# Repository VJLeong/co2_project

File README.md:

#  Automated Compensation of Environmental Changes on CO2 Gas Sensor Response
Project Supervisor: Dr. Ajay Achath Mohanan <br>
Project Members: Leong Van Jun, Vincent Law Yun Kae <br>
Project Commence Date: November 2024 - Present <br>
## Project Description <br>
The main objective of the project is to introduce Artificial Intelligence (AI) and/or machine learning (ML) tools to assist in analysing patterns in obtained carbon dioxide sensor readings and filtering of unwanted noises. <br>
This objective is achieved through proper setting up of the hardware setup and environment of the carbon dioxide sensor. Which is achieved by constructing of appropriate PCB and testing through external microcontroller units. <br>
For this project, the microcontroller unit used is the PSoC 5LP module and PCB design software used is Kicad 8.

## Changelog
### 13/5/2025:
  - Redesigned second version of external chamber PCB --  ready for remanufacturing if needed
  - Updated PID controller for heater controls to P controller (Kp = 120.0f)
### 18/4/2025:
  - Added external chamber PCB schematic design into the repo
  - Begin testing with external chamber PCB prototype
### 23/3/2025:
  - Updated capacitance.py to remove KNN cluster and median filtering algorithm to display raw data output in graph
  - Added heater PID bang-bang control and temperature sensor (3/3 tasks)
### 3/3/2025:
  - Written Python script involving KNN machine learning algorithm to help effeciently filter outlier values in read capacitance values
### 22/2/2025:
  - Re-updated read_capacitance function
  - Included improved analogue circuitry to measure capacitance, now using an
    NE556N timer module instead of simple RC circuit (LTSpice file included!)
### 13/2/2025:
  - Completed two tasks of three: Measure capacitance via PSoC
  - Currently debugging capacitance value, current capacitance value too small!
### 12/2/2025: 
  - Uploaded PSoC Creator and Kicad project files into Github repo for the first time.
  - Completed one task of three: Interface SCD30 on PCB with PSoC 5LP to obtain CO2 concentration, temperature, and relative humidity levels (rh%)

## Reference Materials
SCD30 item website: https://sensirion.com/products/catalog/SCD30 <br>
SCD30 Datasheet: https://sensirion.com/media/documents/4EAF6AF8/61652C3C/Sensirion_CO2_Sensors_SCD30_Datasheet.pdf <br>
SCD30 Interface Description: https://sensirion.com/media/documents/D7CEEF4A/6165372F/Sensirion_CO2_Sensors_SCD30_Interface_Description.pdf <br>
SCD30 Example Code: https://github.com/Sensirion/embedded-scd/releases/tag/2.1.1 <br>

## Acknowledgement
Thank you to Dr. Ajay for his supervision and guidance for the project members throughout the project duration.

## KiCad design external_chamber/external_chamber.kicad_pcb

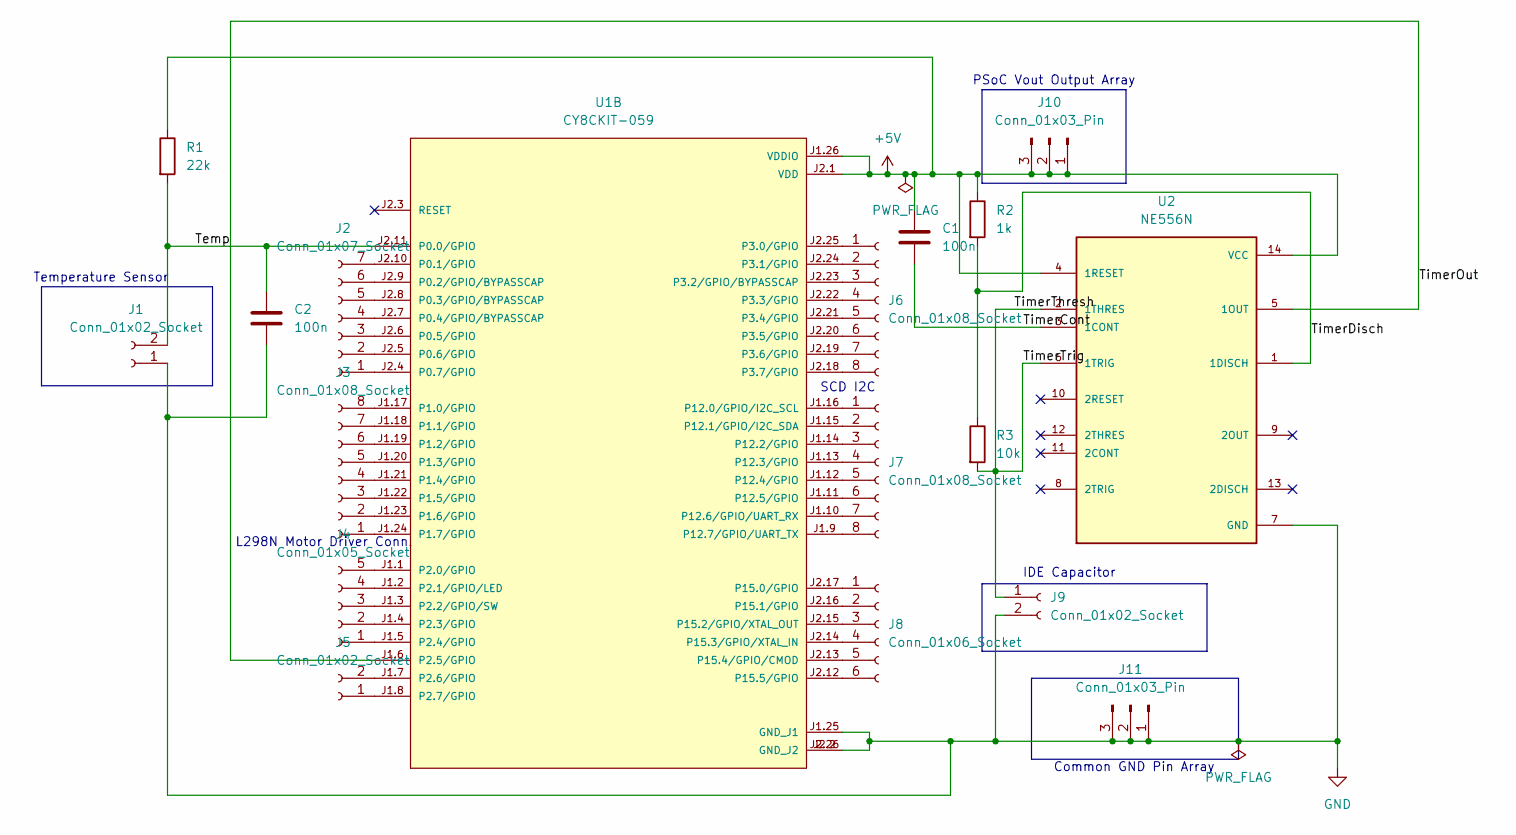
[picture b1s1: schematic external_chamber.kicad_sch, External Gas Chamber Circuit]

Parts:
C1, C2: 100n; C_Disc_D5.0mm_W2.5mm_P5.00mm
J1: Conn_01x02_Socket; PinHeader_1x02_P2.54mm_Vertical
J2: Conn_01x07_Socket; PinSocket_1x07_P2.54mm_Vertical
J3, J6: Conn_01x08_Socket; PinSocket_1x08_P2.54mm_Vertical
J4: Conn_01x05_Socket; PinSocket_1x05_P2.54mm_Vertical
J5, J9: Conn_01x02_Socket; PinSocket_1x02_P2.54mm_Vertical
J7: Conn_01x08_Socket; PinHeader_1x08_P2.54mm_Vertical
J8: Conn_01x06_Socket; PinSocket_1x06_P2.54mm_Vertical
J10, J11: Conn_01x03_Pin; PinSocket_1x03_P2.54mm_Vertical
R1: 22k; R_Axial_DIN0207_L6.3mm_D2.5mm_P7.62mm_Horizontal
R2: 1k; R_Axial_DIN0207_L6.3mm_D2.5mm_P7.62mm_Horizontal
R3: 10k; R_Axial_DIN0207_L6.3mm_D2.5mm_P7.62mm_Horizontal
U1: CY8CKIT-059; MODULE_CY8CKIT-059; PARTREV G
U2: NE556N; DIP794W45P254L1930H508Q14; PARTREV JUNE 2006; DigiKey_Part_Number 296-6504-5-ND

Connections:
+5V: C1.1, J10.1, J10.2, J10.3, R1.1, R2.1, U1.J1.26 (VDDIO), U1.J2.1 (VDD), U2.4 (1RESET), U2.14 (VCC)
/Temp: C2.1, J1.2, R1.2, U1.J2.11 (P0.0/GPIO)
/TimerCont: C1.2, U2.3 (1CONT)
/TimerDisch: R2.2, R3.1, U2.1 (1DISCH)
/TimerOut: U1.J1.6 (P2.5/GPIO), U2.5 (1OUT)
/TimerThresh: J9.1, R3.2, U2.2 (1THRES), U2.6 (1TRIG)
GND: C2.2, J1.1, J9.2, J11.1, J11.2, J11.3, U1.J1.25 (GND_J1), U1.J2.2 (GND_J2), U1.J2.26 (GND_J2), U2.7 (GND)
unnamed: J2.1, U1.J2.4 (P0.7/GPIO)
unnamed: J2.2, U1.J2.5 (P0.6/GPIO)
unnamed: J2.3, U1.J2.6 (P0.5/GPIO)
unnamed: J2.4, U1.J2.7 (P0.4/GPIO/BYPASSCAP)
unnamed: J2.5, U1.J2.8 (P0.3/GPIO/BYPASSCAP)
unnamed: J2.6, U1.J2.9 (P0.2/GPIO/BYPASSCAP)
unnamed: J2.7, U1.J2.10 (P0.1/GPIO)
unnamed: J3.1, U1.J1.24 (P1.7/GPIO)
unnamed: J3.2, U1.J1.23 (P1.6/GPIO)
unnamed: J3.3, U1.J1.22 (P1.5/GPIO)
unnamed: J3.4, U1.J1.21 (P1.4/GPIO)
unnamed: J3.5, U1.J1.20 (P1.3/GPIO)
unnamed: J3.6, U1.J1.19 (P1.2/GPIO)
unnamed: J3.7, U1.J1.18 (P1.1/GPIO)
unnamed: J3.8, U1.J1.17 (P1.0/GPIO)
unnamed: J4.1, U1.J1.5 (P2.4/GPIO)
unnamed: J4.2, U1.J1.4 (P2.3/GPIO)
unnamed: J4.3, U1.J1.3 (P2.2/GPIO/SW)
unnamed: J4.4, U1.J1.2 (P2.1/GPIO/LED)
unnamed: J4.5, U1.J1.1 (P2.0/GPIO)
unnamed: J5.1, U1.J1.8 (P2.7/GPIO)
unnamed: J5.2, U1.J1.7 (P2.6/GPIO)
unnamed: J6.1, U1.J2.25 (P3.0/GPIO)
unnamed: J6.2, U1.J2.24 (P3.1/GPIO)
unnamed: J6.3, U1.J2.23 (P3.2/GPIO/BYPASSCAP)
unnamed: J6.4, U1.J2.22 (P3.3/GPIO)
unnamed: J6.5, U1.J2.21 (P3.4/GPIO)
unnamed: J6.6, U1.J2.20 (P3.5/GPIO)
unnamed: J6.7, U1.J2.19 (P3.6/GPIO)
unnamed: J6.8, U1.J2.18 (P3.7/GPIO)
unnamed: J7.1, U1.J1.16 (P12.0/GPIO/I2C_SCL)
unnamed: J7.2, U1.J1.15 (P12.1/GPIO/I2C_SDA)
unnamed: J7.3, U1.J1.14 (P12.2/GPIO)
unnamed: J7.4, U1.J1.13 (P12.3/GPIO)
unnamed: J7.5, U1.J1.12 (P12.4/GPIO)
unnamed: J7.6, U1.J1.11 (P12.5/GPIO)
unnamed: J7.7, U1.J1.10 (P12.6/GPIO/UART_RX)
unnamed: J7.8, U1.J1.9 (P12.7/GPIO/UART_TX)
unnamed: J8.1, U1.J2.17 (P15.0/GPIO)
unnamed: J8.2, U1.J2.16 (P15.1/GPIO)
unnamed: J8.3, U1.J2.15 (P15.2/GPIO/XTAL_OUT)
unnamed: J8.4, U1.J2.14 (P15.3/GPIO/XTAL_IN)
unnamed: J8.5, U1.J2.13 (P15.4/GPIO/CMOD)
unnamed: J8.6, U1.J2.12 (P15.5/GPIO)

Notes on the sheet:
SCD I2C
IDE Capacitor
PSoC Vout Output Array
Common GND Pin Array
Temperature Sensor
L298N Motor Driver Conn.

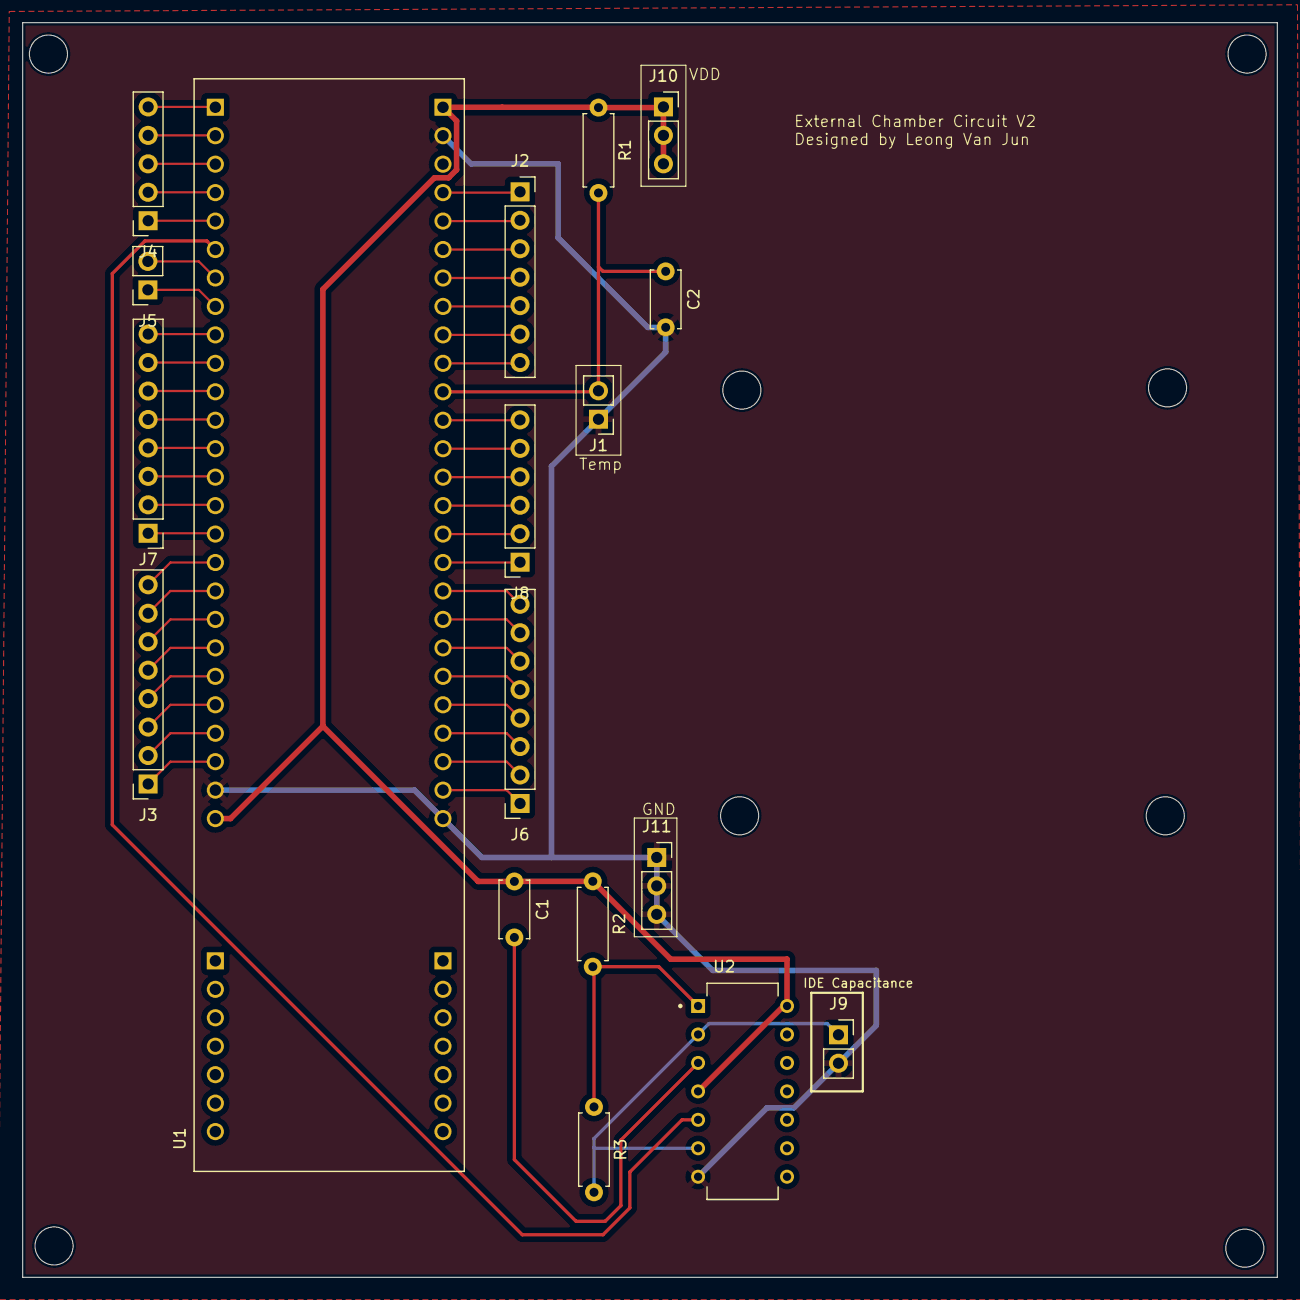
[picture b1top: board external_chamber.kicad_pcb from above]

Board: 2 copper layers, 112.0 x 112.0 mm, 18 parts (0 on the bottom side), 51 nets.

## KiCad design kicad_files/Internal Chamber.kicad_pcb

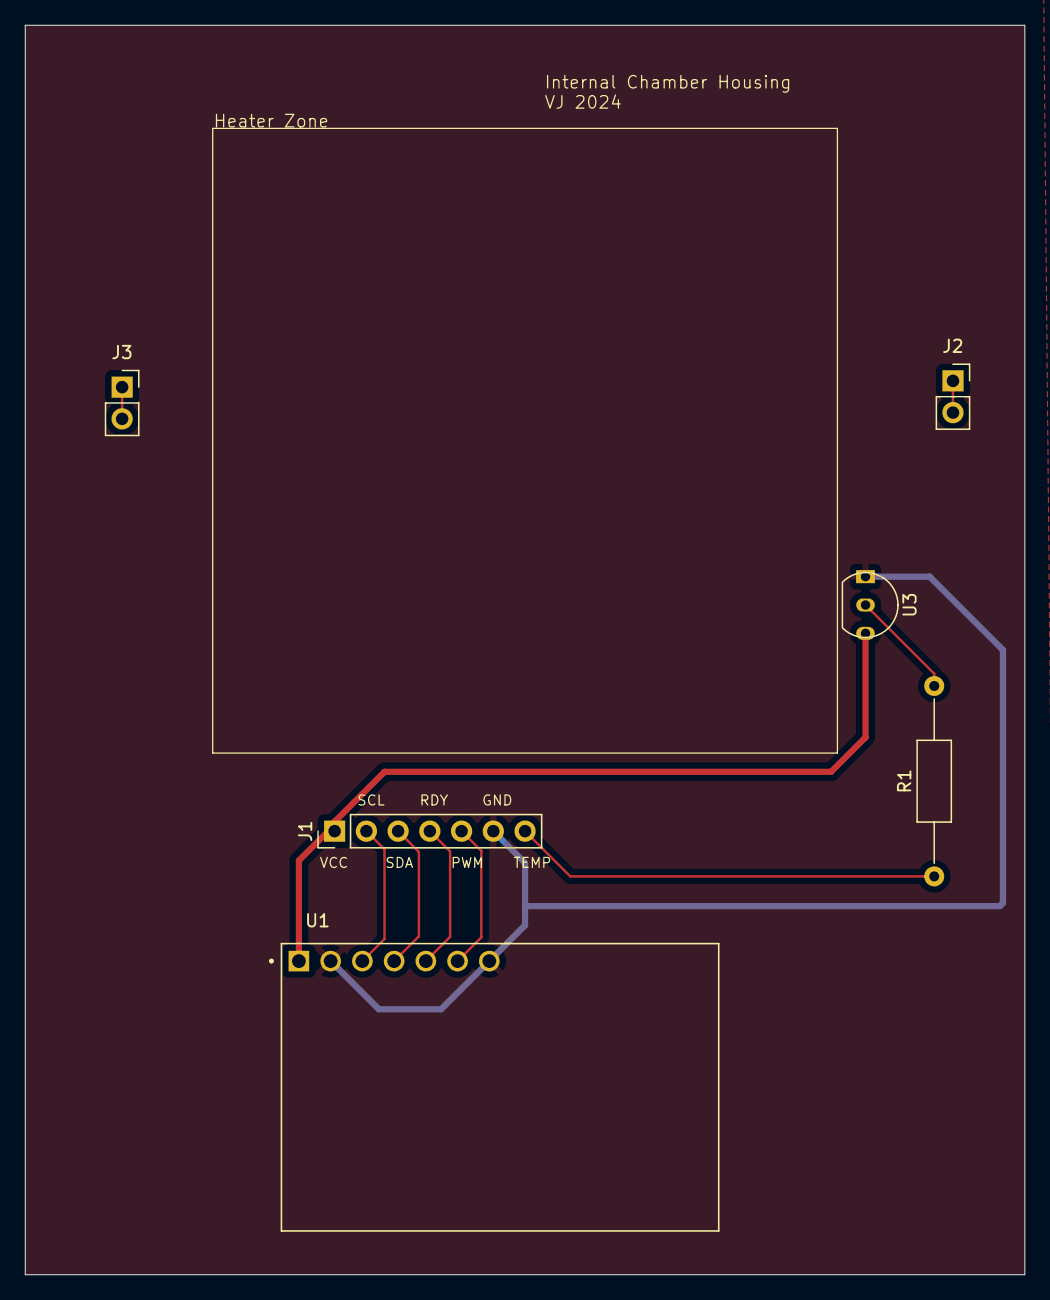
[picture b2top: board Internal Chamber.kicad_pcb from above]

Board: 2 copper layers, 80.0 x 100.0 mm, 6 parts (0 on the bottom side), 9 nets.

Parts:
J1: Conn_01x07_Pin; PinHeader_1x07_P2.54mm_Vertical
J2, J3: Conn_01x02_Pin; PinSocket_1x02_P2.54mm_Vertical
R1: 4.7k; R_Axial_DIN0207_L6.3mm_D2.5mm_P15.24mm_Horizontal
U1: SCD30; MODULE_SCD30
U3: DS18B20; TO-92_Inline

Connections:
/Data: J2.1, J2.2, J3.1, J3.2
/PWM: J1.5, U1.6 (PWM)
/RDY: J1.4, U1.5 (RDY)
/SCL: J1.2, U1.3 (TX/SCL)
/SDA: J1.3, U1.4 (RX/SDA)
/TEMP: J1.7, R1.1
/VCC: J1.1, U1.1 (VDD), U3.3 (V_{DD})
GND: J1.6, U1.2 (GND), U1.7 (SEL), U3.1 (GND)
unnamed: R1.2, U3.2 (DQ)

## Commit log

2025-02-12 First commit into GitHub!
2025-02-12 Added .gitignore
2025-02-12 Added Kicad Files for reference and updated .gitignore file
2025-02-12 Tidy up code and test pushing
2025-02-13 Added capacitance measurement, debugging required
2025-02-22 Updated capacitance measurement capability and added LTSpice circuit diagram of updated capacitance measuring circuit
2025-02-22 Date typo in readme
2025-03-03 Added capacitor.py to track and filter capacitance values
2025-03-03 Updated capacitance.py to output final measured output
2025-03-23 Added heater controls and temperature sensing
2025-03-23 Updated temperature sensing sensitivity, getting ready to turn into RTOS
2025-03-23 Further updates for heater controls
2025-04-18 Added external chamber PCB design files and schematic diagram
2025-05-13 Updated heater controls and uploaded re-design of external chamber PCB
